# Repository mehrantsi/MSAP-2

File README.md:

# MSAP-2

An 8-bit discrete-logic computer - the successor to [MSAP-1](https://github.com/mehrantsi/MSAP-1). Where MSAP-1 is a 256-byte SAP-1 derivative, MSAP-2 is a small but real computer: 8-bit variable-length opcodes driven by microcode in four 28C256 control ROMs, an 8KB address space split between a MOS operating-system ROM and user RAM, a hardware stack, vectored interrupts, a serial console, and an SD-card disk - programmable and usable entirely from its own terminal.

| Aspect | Description |
|---|---|
| Datapath | A, X (up/down counters), SP, 13-bit PC, hidden B operand register, 74HC181 ALU |
| Control | 32-bit control word from 4x 28C256, address = flags(3) \| opcode(8) \| step(4), 16 T-states/instruction max |
| Memory | 28C64 MOS ROM at `0x0000-0x0FFF`, HM6264 SRAM above; 13-bit MAR with a 4-way source mux and TMP+X index adder |
| Interrupts | IRQ pushes PC + flags and vectors through RAM at `0x1F1A`; BRK is a software breakpoint into the monitor |
| I/O | ACIA console (RX/TX status bits), SD disk with ready handshake, 7-seg display, 16-bit counter/comparator timer |
| Software | [MOS 1.1](https://github.com/mehrantsi/MOS-1) monitor (resident line assembler, disk filesystem, run-by-name) + EDIT, a disk-loaded editor/assembler with labels |

## Layout

- **[simulator/](simulator)** - the microcode-accurate simulator: 3D/2D bench, terminal, logic analyzer, oscilloscope, PSU model, microcode editor with EEPROM export, KiCad netlist/PCB export. `npm run dev` to run, `npm test` for the headless self-test that boots MOS and drives it end to end.
- **[Schematics/](Schematics)** - generated KiCad netlist and PCB files plus per-board schematic sheets (SVG/PNG), all derived from the simulator's module registry. See its README for the generation flow.
- The OS and EDIT live in [MOS-1](https://github.com/mehrantsi/MOS-1); the cross assembler (`msap-asm --isa msap2`) lives in [8-bit_CPU_Programmer](https://github.com/mehrantsi/8-bit_CPU_Programmer).

## Status

rev.A: the CPU executes from control-ROM images (no instruction logic outside them), the OS boots from a write-protected ROM image assembled by the real toolchain, every chip on every board carries declared pin nets, and both EEPROM sets (4 control ROMs + OS ROM) export as burnable binaries. Remaining before fabrication: route the exported PCB in KiCad and capture the rev.A schematic there from the netlist.

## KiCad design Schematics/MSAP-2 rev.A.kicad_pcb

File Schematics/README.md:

# MSAP-2 rev.A schematics

Everything in this folder is **generated from the simulator's module registry** (`../simulator/src/core/modules.ts`) - the same data the simulation, power model, and inspector run on. Nothing is drawn by hand, so the schematic can never drift from the machine that was verified.

## Files

- `MSAP-2 rev.A.net` - KiCad netlist: every component with footprint, every declared pin net, plus VCC/GND. Import into pcbnew via File > Import Netlist.
- `MSAP-2 rev.A.kicad_pcb` - single consolidated board, through-hole footprints, flow-packed by module with silkscreen labels and net assignments. **Unrouted** - this is the layout starting point.
- `MSAP-2 rev.A SMD.kicad_pcb` - the same board with SMD-equivalent footprints (SOIC/SOT).
- `KiCad/` - one `.kicad_sch` per board (KiCad 7+): every component as a symbol with its real pin count, nets attached as global labels at the pin tips. Open directly in eeschema, or plot from there.
- `SVG/`, `PNGs/` - one sheet per board (clock, PC, registers, stack pointer, ALU, RAM/ROM, control, terminal+disk IO, display, address path), rendered by the simulator's schematic view with routed same-net wires, in the classic KiCad light theme.

## Regenerating

`node scripts/export-schematics.mjs` in `../simulator` regenerates the netlist and both PCB variants after any registry change; the in-app Export menu produces the same files interactively. The per-board sheets come from the app's Schematic view (the SVGs are its exact render). The EEPROM contents (4x control ROM `.bin` from the Microcode panel, `mos.bin` / `ed.bin` from `~/dev/MOS-1/build.sh`) complete the burnable artifact set.

## Status vs MSAP-1

MSAP-1's `Schematics/` holds the hand-captured KiCad project for hardware that exists. MSAP-2 rev.A is the inverse flow: the registry is the source of truth, these files are its export, and the remaining manual steps before fabrication are routing the PCB and (optionally) capturing a hand-drawn `.kicad_sch` from the netlist for documentation.

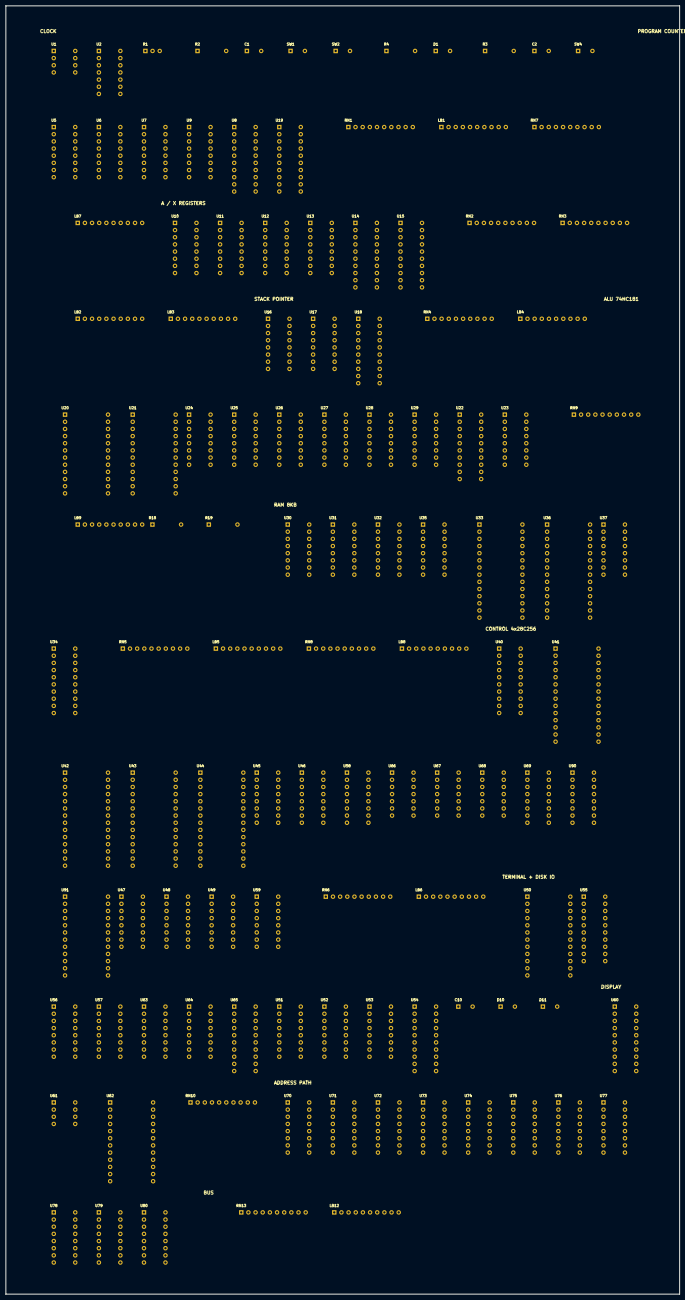
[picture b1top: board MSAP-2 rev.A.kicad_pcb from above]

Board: 2 copper layers, 239.0 x 457.0 mm, 114 parts (0 on the bottom side), 271 nets, no tracks yet.

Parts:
C1: 10nF; C_Disc_D5.0mm_W2.5mm_P5.00mm
C2: 10uF; C_Disc_D5.0mm_W2.5mm_P5.00mm
C10: 100nF; C_Disc_D5.0mm_W2.5mm_P5.00mm
D1: clk; LED_D3.0mm
D10: rx; LED_D3.0mm
D11: tx; LED_D3.0mm
LB1: PC LO; DIP-20_W7.62mm
LB2: A; DIP-20_W7.62mm
LB3: X; DIP-20_W7.62mm
LB4: SP; DIP-20_W7.62mm
LB5: ADDR; DIP-20_W7.62mm
LB6: OPC; DIP-20_W7.62mm
LB7: PC HI; DIP-20_W7.62mm
LB8: ADDR HI; DIP-20_W7.62mm
LB9: FLAGS; DIP-20_W7.62mm
LB12: BUS; DIP-20_W7.62mm
R1: 1M; Potentiometer_Bourns_3296W_Vertical
R2: 1K; R_Axial_DIN0207_L6.3mm_D2.5mm_P10.16mm_Horizontal
R3: 10K; R_Axial_DIN0207_L6.3mm_D2.5mm_P10.16mm_Horizontal
R4, R18, R19: 470; R_Axial_DIN0207_L6.3mm_D2.5mm_P10.16mm_Horizontal
RN1, RN6: 470x9; R_Array_SIP9
RN2, RN3, RN4, RN5, RN10, RN13: 220x9; R_Array_SIP9
RN7: 470x6; R_Array_SIP9
RN8: 220x6; R_Array_SIP9
RN9: 470x5; R_Array_SIP9
SW1: step; SW_PUSH_6mm_H5mm
SW2: mode; SW_PUSH_6mm_H5mm
SW4: reset; SW_PUSH_6mm_H5mm
U1, U61: LM555; DIP-8_W7.62mm
U2: 74HC14; DIP-14_W7.62mm
U5, U6, U7, U9, U45, U47, U48, U49, U56, U57, U59, U63, U64: 74HC161; DIP-16_W7.62mm
U8, U14, U15, U18, U19, U22, U34, U54: 74HC245; DIP-20_W7.62mm
U10, U11, U23, U24, U25, U30, U31, U32, U35: 74HC173; DIP-16_W7.62mm
U12, U13, U16, U17: 74HC193; DIP-16_W7.62mm
U20, U21: 74HC181; DIP-24_W15.24mm
U26, U27, U28, U29: 74HC157; DIP-16_W7.62mm
U33: HM6264; DIP-28_W15.24mm
U36: AT28C64; DIP-28_W15.24mm
U37, U46, U51, U58, U69, U90: 74HC138; DIP-16_W7.62mm
U40, U55, U60: 74HC273; DIP-20_W7.62mm
U41, U42, U43, U44: AT28C256; DIP-28_W15.24mm
U50: MC6850; DIP-24_W15.24mm
U52: 74HC595; DIP-16_W7.62mm
U53: 74HC165; DIP-16_W7.62mm
U62, U91: AT28C16; DIP-24_W15.24mm
U65: 74HC688; DIP-20_W7.62mm
U66, U67, U68: 74HC00; DIP-14_W7.62mm
U70, U71, U72, U73, U74, U75, U76: 74HC153; DIP-16_W7.62mm
U77, U78, U79, U80: 74HC283; DIP-16_W7.62mm

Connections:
555_DIS: R1.1, R2.2, U1.7
555_OUT: U1.3, U2.1
555_THR: C1.1, R1.2, U1.2, U1.6
A0: LB2.1, RN2.2, U10.3, U14.2, U28.2
A1: LB2.2, RN2.3, U10.4, U14.3, U28.5
A2: LB2.3, RN2.4, U10.5, U14.4, U28.14
A3: LB2.4, RN2.5, U10.6, U14.5, U28.11
A4: LB2.5, RN2.6, U11.3, U14.6, U29.2
A5: LB2.6, RN2.7, U11.4, U14.7, U29.5
A6: LB2.7, RN2.8, U11.5, U14.8, U29.14
A7: LB2.8, RN2.9, U11.6, U14.9, U29.11
AI~: U10.9, U10.10, U11.9, U11.10, U66.3
ALC: U20.7, U91.15
ALC4: U20.16, U21.7
ALCO: U21.16, U23.14
ALF0: U20.9, U26.2
ALF1: U20.10, U26.3, U26.5
ALF2: U20.11, U26.6, U26.14
ALF3: U20.13, U26.11, U26.13
ALF4: U21.9, U26.10, U27.2
ALF5: U21.10, U27.3, U27.5
ALF6: U21.11, U27.6, U27.14
ALF7: U21.13, U23.12, U27.11, U27.13
ALM: U20.8, U21.8, U91.14
ALO0: U22.2, U26.4
ALO1: U22.3, U26.7
ALO2: U22.4, U26.12
ALO3: U22.5, U26.9
ALO4: U22.6, U27.4
ALO5: U22.7, U27.7
ALO6: U22.8, U27.12
ALO7: U22.9, U27.9
ALS0: U20.6, U21.6, U91.9
ALS1: U20.5, U21.5, U91.10
ALS2: U20.4, U21.4, U91.11
ALS3: U20.3, U21.3, U91.13
ALSHR: U26.1, U27.1, U91.16
AO~: U14.19, U46.13
AS0: U20.2, U28.4
AS1: U20.23, U28.7
AS2: U20.21, U28.12
AS3: U20.19, U28.9
AS4: U21.2, U29.4
AS5: U21.23, U29.7
AS6: U21.21, U29.12
AS7: U21.19, U29.9
AXS: U28.1, U29.1
B0: U20.1, U24.3
B1: U20.22, U24.4
B2: U20.20, U24.5
B3: U20.18, U24.6
B4: U21.1, U25.3
B5: U21.22, U25.4
B6: U21.20, U25.5
B7: U21.18, U25.6
BI~: U24.9, U24.10, U25.9, U25.10, U66.6
BUS0: LB12.1, RN13.2, U8.18, U10.14, U12.15, U14.18, U15.18, U16.15, U18.18, U19.18, U22.18, U24.14, U34.18, U40.3, U47.3, U49.3, U50.22, U54.18, U55.3, U60.3
BUS1: LB12.2, RN13.3, U8.17, U10.13, U12.1, U14.17, U15.17, U16.1, U18.17, U19.17, U22.17, U24.13, U34.17, U40.4, U47.4, U49.4, U50.21, U54.17, U55.4, U60.4
BUS2: LB12.3, RN13.4, U8.16, U10.12, U12.10, U14.16, U15.16, U16.10, U18.16, U19.16, U22.16, U24.12, U34.16, U40.7, U47.5, U49.5, U50.20, U54.16, U55.7, U60.7
BUS3: LB12.4, RN13.5, U8.15, U10.11, U12.9, U14.15, U15.15, U16.9, U18.15, U19.15, U22.15, U24.11, U34.15, U40.8, U47.6, U49.6, U50.19, U54.15, U55.8, U60.8
BUS4: LB12.5, RN13.6, U8.14, U11.14, U13.15, U14.14, U15.14, U17.15, U18.14, U19.14, U22.14, U25.14, U34.14, U40.13, U48.3, U50.18, U54.14, U55.13, U59.3, U60.13
BUS5: LB12.6, RN13.7, U8.13, U11.13, U13.1, U14.13, U15.13, U17.1, U18.13, U22.13, U25.13, U34.13, U40.14, U48.4, U50.17, U54.13, U55.14, U59.4, U60.14
BUS6: LB12.7, RN13.8, U8.12, U11.12, U13.10, U14.12, U15.12, U17.10, U18.12, U22.12, U25.12, U34.12, U40.17, U48.5, U50.16, U54.12, U55.17, U59.5, U60.17
BUS7: LB12.8, RN13.9, U8.11, U11.11, U13.9, U14.11, U15.11, U17.9, U18.11, U22.11, U25.11, U34.11, U40.18, U48.6, U50.15, U54.11, U55.18, U59.6, U60.18
CLK: R4.1, U2.2, U2.9, U5.2, U6.2, U7.2, U9.2, U10.7, U11.7, U23.7, U24.7, U25.7, U30.7, U31.7, U32.7, U35.7, U40.11, U47.2, U48.2, U49.2, U50.14, U56.2, U57.2, U59.2, U63.2, U64.2
CLKG: U2.8, U45.2, U66.2, U66.5, U66.10, U66.13, U67.2, U67.5, U67.10, U67.13, U68.2, U68.5, U68.10, U68.13
CW0: U41.11, U46.1, U58.1
CW1: U41.12, U46.2, U58.2
CW2: U41.13, U46.3, U58.3
CW3: U41.15, U46.4, U58.6
CW4: U41.16, U66.1
CW5: U41.17, U68.9
CW6: U41.18, U66.4
CW7: U41.19, U66.9
CW8: U42.11, U66.12
CW9: U42.12, U67.1
CW10: U42.13, U67.4
CW11: U42.15, U67.9
CW12: U42.16, U67.12
CW13: U42.17, U68.1
CW14: U42.18, U70.14, U71.14, U72.14, U73.14, U74.14, U75.14, U76.14
CW15: U42.19, U70.2, U71.2, U72.2, U73.2, U74.2, U75.2, U76.2
CW16: U43.11, U69.1, U90.1
CW17: U43.12, U69.2, U90.2
CW18: U43.13, U69.3, U90.3
CW19: U43.15, U69.4, U90.6
CW20: U43.16, U91.8
CW21: U43.17, U91.7
CW22: U43.18, U91.6
CW23: U43.19, U68.4
CW27: U44.15, U68.12
D1A: D1.1, R4.2
DO~: U54.19, U58.14
DSK_SCK: U52.11, U53.2
EO~: U22.19, U46.10
FC: LB9.1, RN9.2, U23.3, U41.2, U42.2, U43.2, U44.2
FIE: LB9.4, RN9.5, U23.6
FI~: U23.9, U23.10, U68.6
FN: LB9.3, RN9.4, U23.5, U41.1, U42.1, U43.1, U44.1
FZ: LB9.2, RN9.3, U23.4, U41.26, U42.26, U43.26, U44.26
GND: C1.2, C2.2, C10.2, D1.2, D10.2, D11.2, R18.2, R19.2, RN1.1, RN2.1, RN3.1, RN4.1, RN5.1, RN6.1, RN7.1, RN8.1, RN9.1, RN10.1, RN13.1, SW1.2, SW2.2, SW4.2, U1.1, U2.7, U5.8, U6.8, U7.8, U8.10, U9.4, U9.5, U9.6, U9.8, U10.1, U10.2, U10.8, U10.15, U11.1, U11.2, U11.8, U11.15, U12.8, U12.14, U13.8, U13.14, U14.10, U15.10, U16.8, U16.14, U17.8, U17.14, U18.10, U19.7, U19.8, U19.9, U19.10, U20.12, U21.12, U22.10, U23.1, U23.2, U23.8, U23.15, U24.1, U24.2, U24.8, U24.15, U25.1, U25.2, U25.8, U25.15, U26.8, U26.15, U27.8, U27.10, U27.15, U28.8, U28.15, U29.8, U29.15, U30.1, U30.2, U30.8, U30.15, U31.1, U31.2, U31.8, U31.15, U32.1, U32.2, U32.8, U32.15, U33.1, U33.14, U33.26, U34.10, U35.1, U35.2, U35.8, U35.11, U35.12, U35.13, U35.15, U36.1, U36.2, U36.14, U36.26, U37.2, U37.3, U37.4, U37.5, U37.8, U40.10, U41.14, U41.20, U41.22, U42.14, U42.20, U42.22, U43.14, U43.20, U43.22, U44.14, U44.20, U44.22, U45.3, U45.4, U45.5, U45.6, U45.8, U46.5, U46.8, U47.8, U48.8, U49.8, U50.1, U50.9, U51.4, U51.5, U51.8, U52.8, U52.13, U53.8, U53.15, U54.10, U55.10, U56.3, U56.4, U56.5, U56.6, U56.8, U57.3, U57.4, U57.5, U57.6, U57.8, U58.4, U58.5, U58.8, U59.8, U60.10, U61.1, U62.12, U62.18, U62.20, U63.3, U63.4, U63.5, U63.6, U63.8, U64.3, U64.4, U64.5, U64.6, U64.8, U65.1, U65.10, U66.7, U67.7, U68.7, U69.5, U69.8, U70.1, U70.8, U70.15, U71.1, U71.8, U71.15, U72.1, U72.8, U72.15, U73.1, U73.8, U73.15, U74.1, U74.8, U74.15, U75.1, U75.8, U75.15, U76.1, U76.8, U76.10, U76.11, U76.12, U76.13, U76.15, U77.7, U77.8, U78.8, U79.2, U79.6, U79.8, U79.11, U79.15, U80.2, U80.6, U80.8, U80.11, U80.15, U90.4, U90.5, U90.8, U91.1, U91.2, U91.3, U91.4, U91.5, U91.12, U91.18, U91.20
IOSEL0~: U50.10, U51.15
IOSEL3~: U51.12, U60.11
IOSEL4~: U51.11, U55.11
IOW: D11.1, U50.3
IOW~: U50.13, U67.11
MAR0: LB5.1, RN5.2, U30.3, U33.10, U36.10, U70.7
MAR1: LB5.2, RN5.3, U30.4, U33.9, U36.9, U70.9
MAR2: LB5.3, RN5.4, U30.5, U33.8, U36.8, U71.7
MAR3: LB5.4, RN5.5, U30.6, U33.7, U36.7, U71.9
MAR4: LB5.5, RN5.6, U31.3, U33.6, U36.6, U72.7
MAR5: LB5.6, RN5.7, U31.4, U33.5, U36.5, U72.9
MAR6: LB5.7, RN5.8, U31.5, U33.4, U36.4, U73.7
MAR7: LB5.8, RN5.9, U31.6, U33.3, U36.3, U73.9
MAR8: LB8.1, RN8.2, U32.3, U33.25, U36.25, U74.7
MAR9: LB8.2, RN8.3, U32.4, U33.24, U36.24, U74.9
MAR10: LB8.3, RN8.4, U32.5, U33.21, U36.21, U75.7
MAR11: LB8.4, RN8.5, U32.6, U33.23, U36.23, U75.9
MAR12: LB8.5, RN8.6, U33.2, U35.3, U37.1, U76.7
MI~: U30.9, U30.10, U31.9, U31.10, U32.9, U32.10, U35.9, U35.10, U68.3
MUX_THR: U61.2, U61.6
OP0: LB6.1, RN6.2, U40.2, U41.6, U42.6, U43.6, U44.6
OP1: LB6.2, RN6.3, U40.5, U41.5, U42.5, U43.5, U44.5
OP2: LB6.3, RN6.4, U40.6, U41.4, U42.4, U43.4, U44.4
OP3: LB6.4, RN6.5, U40.9, U41.3, U42.3, U43.3, U44.3
OP4: LB6.5, RN6.6, U40.12, U41.25, U42.25, U43.25, U44.25
OP5: LB6.6, RN6.7, U40.15, U41.24, U42.24, U43.24, U44.24
OP6: LB6.7, RN6.8, U40.16, U41.21, U42.21, U43.21, U44.21
OP7: LB6.8, RN6.9, U40.19, U41.23, U42.23, U43.23, U44.23
OUTR0: U60.2, U62.8
OUTR1: U60.5, U62.7
OUTR2: U60.6, U62.6
OUTR3: U60.9, U62.5
OUTR4: U60.12, U62.4
OUTR5: U60.15, U62.3
OUTR6: U60.16, U62.2
OUTR7: U60.19, U62.1
PC0: LB1.1, RN1.2, U5.14, U8.2, U70.6
PC1: LB1.2, RN1.3, U5.13, U8.3, U70.10
PC2: LB1.3, RN1.4, U5.12, U8.4, U71.6
PC3: LB1.4, RN1.5, U5.11, U8.5, U71.10
PC4: LB1.5, RN1.6, U6.14, U8.6, U72.6
PC5: LB1.6, RN1.7, U6.13, U8.7, U72.10
PC6: LB1.7, RN1.8, U6.12, U8.8, U73.6
PC7: LB1.8, RN1.9, U6.11, U8.9, U73.10
PC8: LB7.1, RN7.2, U7.14, U19.2, U74.6
PC9: LB7.2, RN7.3, U7.13, U19.3, U74.10
PC10: LB7.3, RN7.4, U7.12, U19.4, U75.6
PC11: LB7.4, RN7.5, U7.11, U19.5, U75.10
PC12: LB7.5, RN7.6, U9.14, U19.6, U76.6
PCC1: U5.15, U6.7, U6.10
PCC2: U6.15, U7.7, U7.10
PCC3: U7.15, U9.7, U9.10
PCHO~: U19.19, U58.15
PCI: U5.7, U5.10, U69.14
PCLD~: U5.9, U6.9, U7.9, U9.9, U69.13
PCLO~: U8.19, U46.7
RAMCS~: U33.20, U37.14
RD0: U33.11, U34.2, U36.11
RD1: U33.12, U34.3, U36.12
RD2: U33.13, U34.4, U36.13
RD3: U33.15, U34.5, U36.15
RD4: U33.16, U34.6, U36.16
RD5: U33.17, U34.7, U36.17
RD6: U33.18, U34.8, U36.18
RD7: U33.19, U34.9, U36.19
RESP: U2.4, U2.5
RES_RC: C2.1, R3.2, SW4.1, U2.3
RES~: U2.6, U5.1, U6.1, U7.1, U9.1, U40.1, U47.1, U48.1, U49.1, U55.1, U59.1, U60.1
ROMCS~: U36.20, U37.15
RO~: U33.22, U34.19, U36.22, U46.14
RST~: U45.1, U68.11
RW~: U33.27, U67.8
SEG_A: RN10.2, U62.9
SEG_B: RN10.3, U62.10
SEG_C: RN10.4, U62.11
SEG_D: RN10.5, U62.13
SEG_DP: RN10.9, U62.17
SEG_E: RN10.6, U62.14
SEG_F: RN10.7, U62.15
SEG_G: RN10.8, U62.16
SP0: LB4.1, RN4.2, U16.3, U18.2, U70.4
SP1: LB4.2, RN4.3, U16.2, U18.3, U70.12
SP2: LB4.3, RN4.4, U16.6, U18.4, U71.4
SP3: LB4.4, RN4.5, U16.7, U18.5, U71.12
SP4: LB4.5, RN4.6, U17.3, U18.6, U72.4
SP5: LB4.6, RN4.7, U17.2, U18.7, U72.12
SP6: LB4.7, RN4.8, U17.6, U18.8, U73.4
SP7: LB4.8, RN4.9, U17.7, U18.9, U73.12
SPCB: U16.13, U17.4
SPCU: U16.12, U17.5
SPDN: U16.4, U69.11
SPL~: U16.11, U17.11, U69.10
SPU: U16.5, U69.12
STEP0: U41.10, U42.10, U43.10, U44.10, U45.14
STEP1: U41.9, U42.9, U43.9, U44.9, U45.13
STEP2: U41.8, U42.8, U43.8, U44.8, U45.12
STEP3: U41.7, U42.7, U43.7, U44.7, U45.11
TCC1: U56.15, U57.7, U57.10
TCC2: U57.15, U63.7, U63.10
TCC3: U63.15, U64.7, U64.10
TCT8: U63.14, U65.2
TCT9: U63.13, U65.4
TCT10: U63.12, U65.6
TCT11: U63.11, U65.8
TCT12: U64.14, U65.11
TCT13: U64.13, U65.13
TCT14: U64.12, U65.15
TCT15: U64.11, U65.17
TH~: U49.9, U59.9, U67.3
TIRQ~: U56.1, U57.1, U63.1, U64.1, U65.19
TL~: U47.9, U48.9, U66.11
TMP0: U5.3, U47.14, U50.11, U51.1, U70.5, U77.5
TMP1: U5.4, U47.13, U51.2, U70.11, U77.3
TMP2: U5.5, U47.12, U51.3, U71.5, U77.14
TMP3: U5.6, U47.11, U71.11, U77.12
TMP4: U6.3, U48.14, U72.5, U78.5
TMP5: U6.4, U48.13, U72.11, U78.3
TMP6: U6.5, U48.12, U73.5, U78.14
TMP7: U6.6, U48.11, U73.11, U78.12
TMP8: U7.3, U49.14, U74.5, U79.5
TMP9: U7.4, U49.13, U74.11, U79.3
TMP10: U7.5, U49.12, U75.5, U79.14
TMP11: U7.6, U49.11, U75.11, U79.12
TMP12: U9.3, U59.14, U76.5, U80.5
TMP13: U59.13, U80.3
TMP14: U59.12, U80.14
TMP15: U59.11, U80.12
TPC1: U47.15, U48.7, U48.10
TPC2: U48.15, U49.7, U49.10
TPC3: U49.15, U59.7, U59.10
TPI: U47.7, U47.10, U69.9
TPR0: U55.2, U65.3
TPR1: U55.5, U65.5
TPR2: U55.6, U65.7
TPR3: U55.9, U65.9
TPR4: U55.12, U65.12
TPR5: U55.15, U65.14
TPR6: U55.16, U65.16
TPR7: U55.19, U65.18
TX0: U70.3, U77.4
TX1: U70.13, U77.1
TX2: U71.3, U77.13
TX3: U71.13, U77.10
TX4: U72.3, U78.4
TX5: U72.13, U78.1
TX6: U73.3, U78.13
TX7: U73.13, U78.10
TX8: U74.3, U79.4
TX9: U74.13, U79.1
TX10: U75.3, U79.13
TX11: U75.13, U79.10
TX12: U76.3, U80.4
TXC1: U77.9, U78.7
TXC2: U78.9, U79.7
TXC3: U79.9, U80.7
VCC: C10.1, R2.1, R3.1, U1.8, U2.14, U5.16, U6.16, U7.16, U8.1, U8.20, U9.16, U10.16, U11.16, U12.16, U13.16, U14.1, U14.20, U15.1, U15.20, U16.16, U17.16, U18.1, U18.19, U18.20, U19.1, U19.20, U20.24, U21.24, U22.1, U22.20, U23.16, U24.16, U25.16, U26.16, U27.16, U28.16, U29.16, U30.16, U31.16, U32.16, U33.28, U34.1, U34.20, U35.16, U36.27, U36.28, U37.6, U37.16, U40.20, U41.27, U41.28, U42.27, U42.28, U43.27, U43.28, U44.27, U44.28, U45.7, U45.9, U45.10, U45.16, U46.6, U46.16, U47.16, U48.16, U49.16, U50.8, U50.12, U51.6, U51.16, U52.10, U52.16, U53.16, U54.1, U54.20, U55.20, U56.7, U56.9, U56.10, U56.16, U57.9, U57.16, U58.16, U59.16, U60.20, U61.8, U62.24, U63.9, U63.16, U64.9, U64.16, U65.20, U66.14, U67.14, U68.14, U69.6, U69.16, U70.16, U71.16, U72.16, U73.16, U74.4, U74.12, U74.16, U75.4, U75.12, U75.16, U76.4, U76.16, U77.16, U78.16, U79.16, U80.16, U90.16, U91.21, U91.24
X0: LB3.1, RN3.2, U12.3, U15.2, U28.3, U77.6
X1: LB3.2, RN3.3, U12.2, U15.3, U28.6, U77.2
X2: LB3.3, RN3.4, U12.6, U15.4, U28.13, U77.15
X3: LB3.4, RN3.5, U12.7, U15.5, U28.10, U77.11
X4: LB3.5, RN3.6, U13.3, U15.6, U29.3, U78.6
X5: LB3.6, RN3.7, U13.2, U15.7, U29.6, U78.2
X6: LB3.7, RN3.8, U13.6, U15.8, U29.13, U78.15
X7: LB3.8, RN3.9, U13.7, U15.9, U29.10, U78.11
XCB: U12.13, U13.4
XCU: U12.12, U13.5
XD: U12.4, U90.15
XLD~: U12.11, U13.11, U68.8
XO~: U15.19, U46.12
XU: U12.5, U69.7
